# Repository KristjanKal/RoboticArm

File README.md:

# RoboticArm
Roboti käsi, piirilevy on tehty valmiiks

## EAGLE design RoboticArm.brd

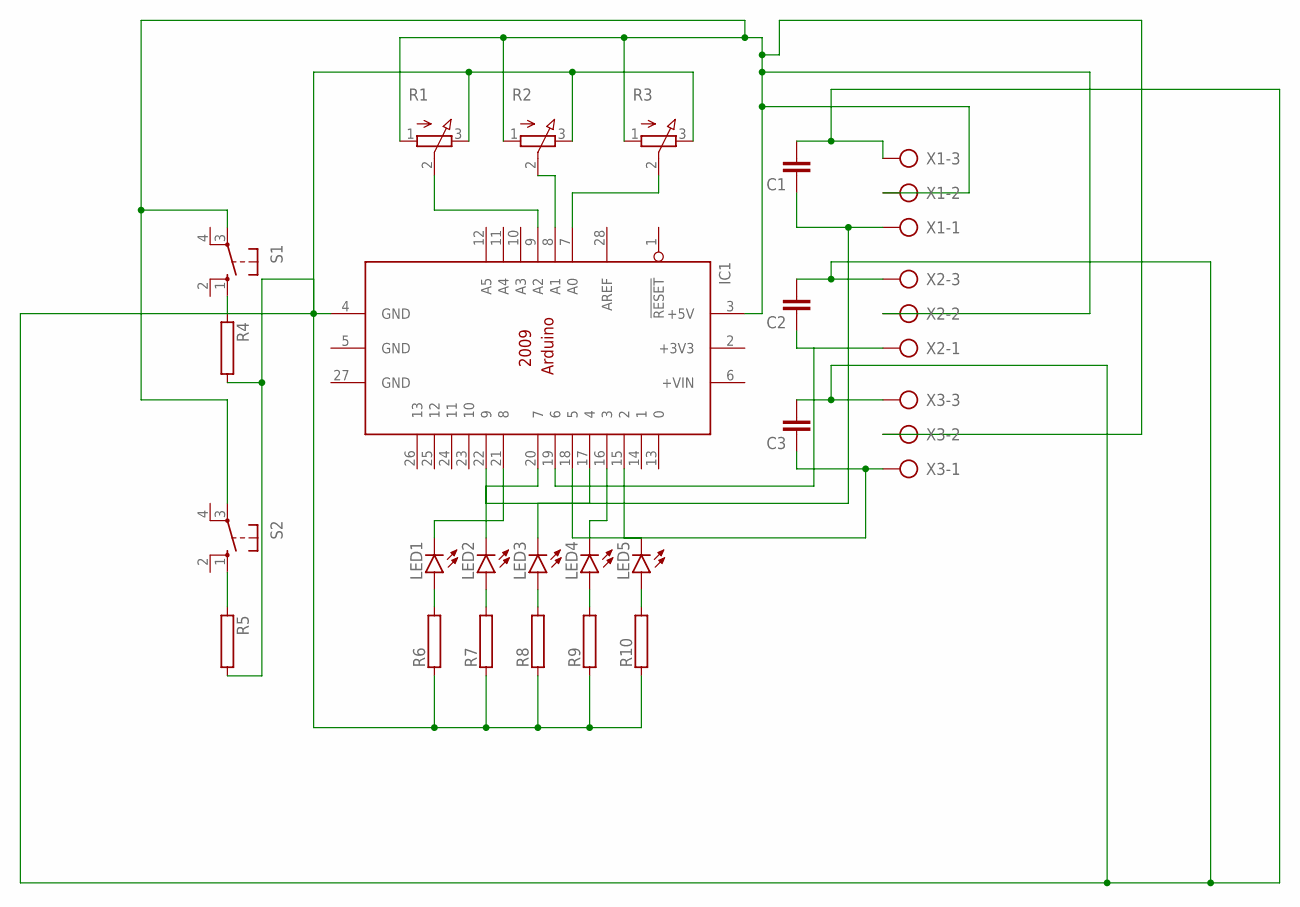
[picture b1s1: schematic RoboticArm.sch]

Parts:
C1, C2, C3: C2.5/2; C2.5-2
IC1: ARDUINO2009_10; ARDUINO2009
LED1, LED2, LED3, LED4, LED5: LED3MM
R1, R2, R3: 3RP/1610N
R4, R5, R6, R7, R8, R9, R10: RAC01; AC01
S1, S2: 10-XX; B3F-10XX
X1, X2, X3: AK300/3

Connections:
+3V3: IC1.2 (+3V3)
GND: IC1.5 (GND), IC1.27 (GND)
unnamed: LED1.A, R6.2
unnamed: IC1.15 (2), LED5.K (C)
unnamed: IC1.16 (3), LED4.K (C)
unnamed: IC1.17 (4), LED3.K (C)
unnamed: IC1.20 (7), LED2.K (C)
unnamed: IC1.21 (8), LED1.K (C)
unnamed: LED2.A, R7.2
unnamed: LED3.A, R8.2
unnamed: LED4.A, R9.2
unnamed: LED5.A, R10.2
unnamed: IC1.7 (A0), R3.2 (S)
unnamed: R4.1, S1.1 (S)
unnamed: R5.1, S2.1 (S)
unnamed: C1.1, IC1.22 (9), X1.1
unnamed: IC1.9 (A2), R1.2 (S)
unnamed: IC1.8 (A1), R2.2 (S)
unnamed: IC1.3 (+5V), R1.1 (A), R2.1 (A), R3.1 (A), S1.3, S2.3, X1.2, X2.2, X3.2
unnamed: C2.1, IC1.19 (6), X2.1
unnamed: C1.2, C2.2, C3.2, IC1.4 (GND), R1.3 (E), R2.3 (E), R3.3 (E), R4.2, R5.2, R6.1, R7.1, R8.1, R9.1, R10.1, X1.3, X2.3, X3.3
unnamed: C3.1, IC1.18 (5), X3.1

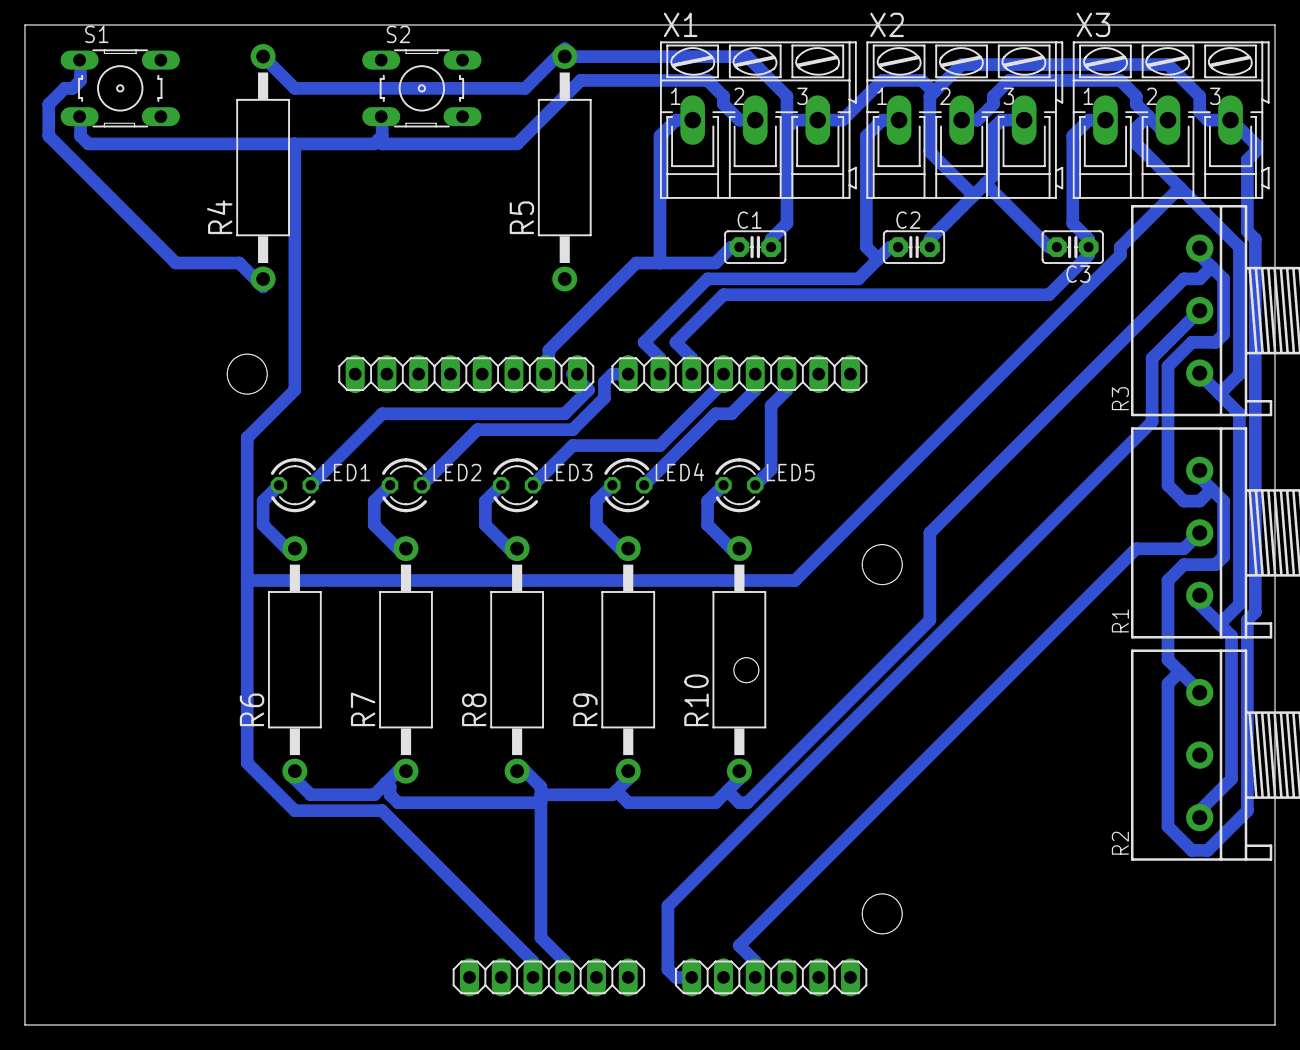
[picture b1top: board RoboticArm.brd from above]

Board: 2 copper layers, 100.0 x 80.0 mm, 24 parts (0 on the bottom side), 21 nets.

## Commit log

2020-01-28 Luoto tiedosto ja laitestto testattu
2020-01-29 Robotikäsi rakennettu valmiiks ja dokumentointu
2020-01-29 Dokumentointtu
2020-01-30 lisä dokumentointi ja lisatty Eagle tiedostot
2020-01-30 lisätty pdf
2020-01-30 dokumentointi poistettu
